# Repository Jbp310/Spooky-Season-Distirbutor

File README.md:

# Spooky-Season-Distirbutor

A candy catapult controlled via a camera capable of detecting humans and a Rasberry pi 4b. 

I plan on developing firmware once I get my hands on the hardware, as I'm sure there will be a myriad of quirks I'll have to account for

As for the hardware, all the files you need should be in the production files folder!

_Designed for Hackclub Halflife!_

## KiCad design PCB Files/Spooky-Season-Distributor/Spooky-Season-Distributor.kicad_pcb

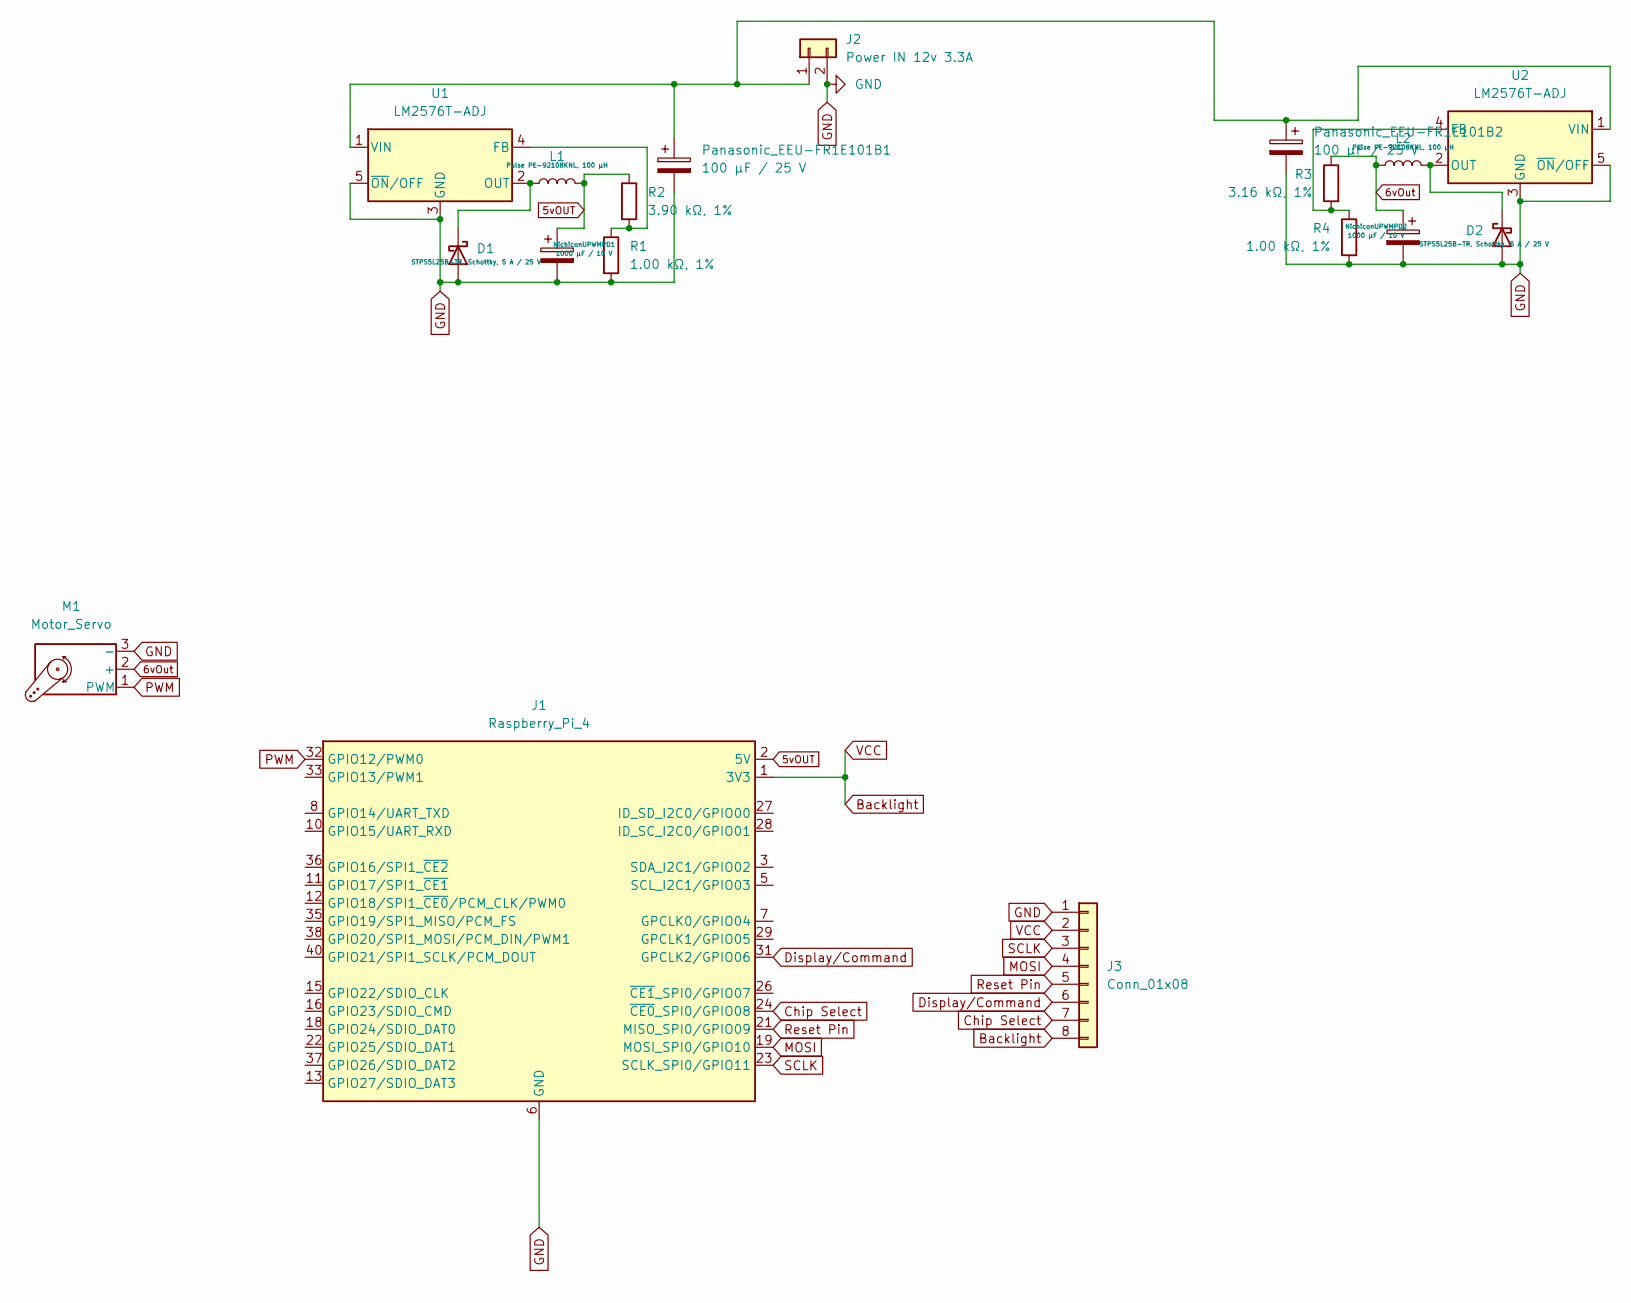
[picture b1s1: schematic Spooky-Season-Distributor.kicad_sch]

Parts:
D1, D2: STPS5L25B-TR, Schottky, 5 A / 25 V; Diode
J1: Raspberry_Pi_4; MODULE_RASPBERRY_PI_4B_4GB
J2: Power IN 12v 3.3A; Power_Con_Solder
J3: Conn_01x08; Display_Solder
L1, L2: Pulse PE-92108KNL, 100 µH; IND_2300LL-271-V-RC
M1: Motor_Servo; Servo_solder
NichiconUPWMPD1, NichiconUPWMPD2: 1000 µF / 10 V; CAPPRR1200W60L1700T850H1800
Panasonic_EEU-FR1E101B1, Panasonic_EEU-FR1E101B2: 100 µF / 25 V; EEU-FR1E101B
R1, R4: 1.00 kΩ, 1%; R_Axial_DIN0207_L6.3mm_D2.5mm_P7.62mm_Horizontal
R2: 3.90 kΩ, 1%; R_Axial_DIN0207_L6.3mm_D2.5mm_P7.62mm_Horizontal
R3: 3.16 kΩ, 1%; R_Axial_DIN0207_L6.3mm_D2.5mm_P7.62mm_Horizontal
U1, U2: LM2576T-ADJ; TO-220-5_Vertical

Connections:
5vOUT: J1.2 (5V), J1.4 (5V), L1.2, NichiconUPWMPD1.1, R2.1
6vOut: L2.2, M1.2 (+), NichiconUPWMPD2.1, R3.1
Backlight: J1.1 (3V3), J1.17 (3V3), J3.2, J3.8
Chip Select: J1.24 (~CE0_SPI0/GPIO08), J3.7
Display/Command: J1.31 (GPCLK2/GPIO06), J3.6
GND: D1.2 (A), D2.2 (A), J1.6 (GND), J1.9 (GND), J1.14 (GND), J1.20 (GND), J1.25 (GND), J1.30 (GND), J1.34 (GND), J1.39 (GND), J2.2, J3.1, M1.3 (-), NichiconUPWMPD1.2, NichiconUPWMPD2.2, Panasonic_EEU-FR1E101B1.2, Panasonic_EEU-FR1E101B2.2, R1.2, R4.2, U1.3 (GND), U1.5 (~ON/OFF), U2.3 (GND), U2.5 (~ON/OFF)
MOSI: J1.19 (MOSI_SPI0/GPIO10), J3.4
unnamed: D1.1 (K), L1.1, U1.2 (OUT)
unnamed: D2.1 (K), L2.1, U2.2 (OUT)
unnamed: J2.1, Panasonic_EEU-FR1E101B1.1, Panasonic_EEU-FR1E101B2.1, U1.1 (VIN), U2.1 (VIN)
unnamed: R1.1, R2.2, U1.4 (FB)
unnamed: R3.2, R4.1, U2.4 (FB)
PWM: J1.32 (GPIO12/PWM0), M1.1 (PWM)
Reset Pin: J1.21 (MISO_SPI0/GPIO09), J3.5
SCLK: J1.23 (SCLK_SPI0/GPIO11), J3.3

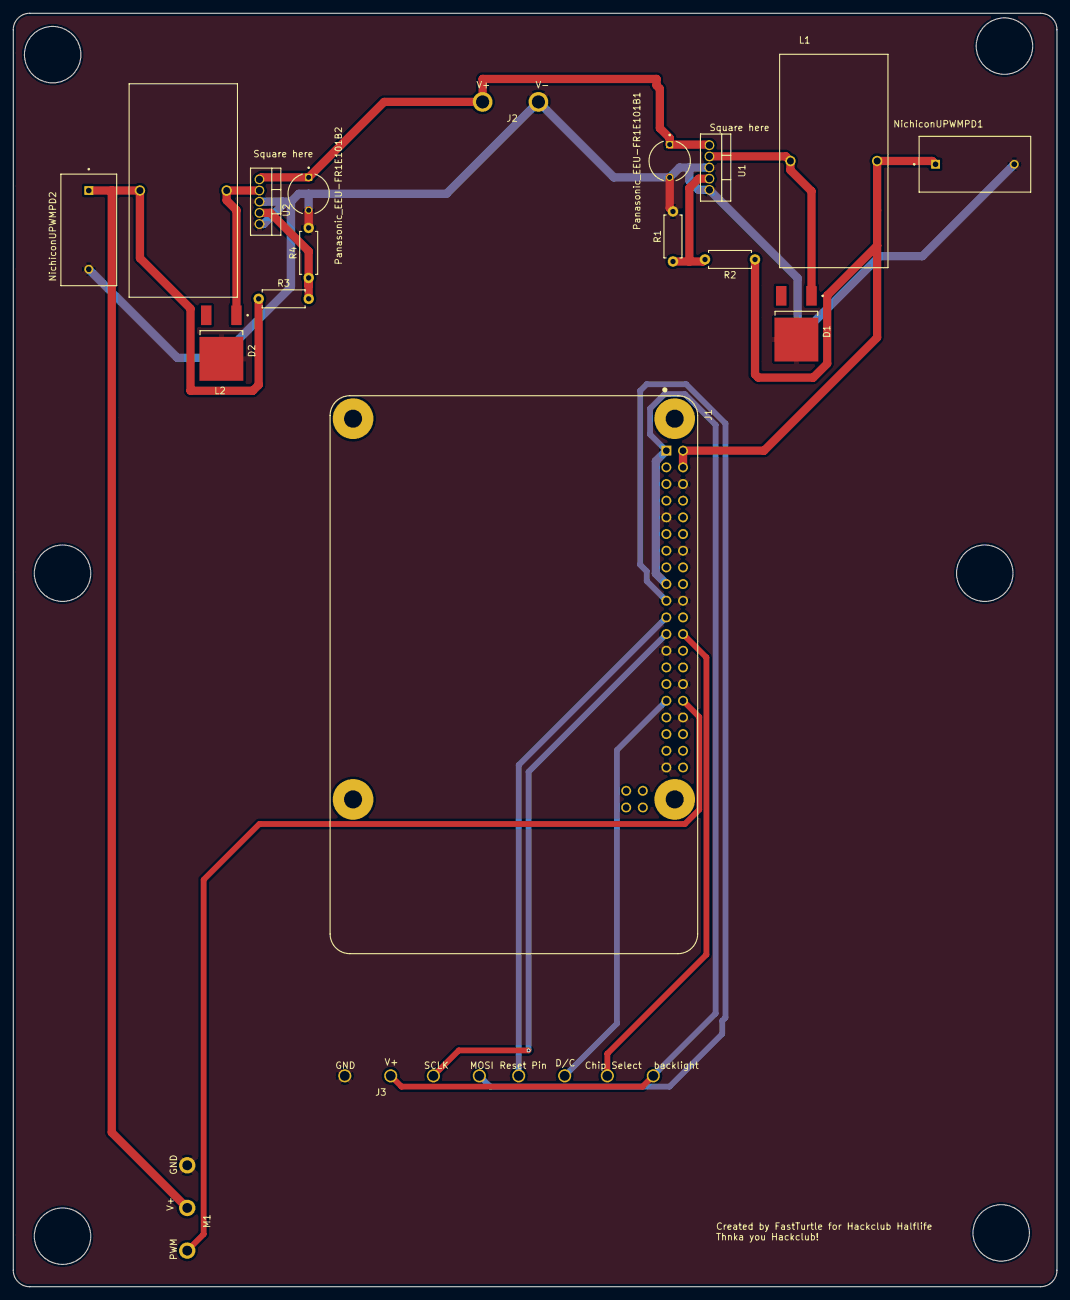
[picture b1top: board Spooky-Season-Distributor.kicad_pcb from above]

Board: 2 copper layers, 159.0 x 194.0 mm, 18 parts (0 on the bottom side), 15 nets.
